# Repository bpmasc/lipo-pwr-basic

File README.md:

# lipo-pwr-basic
Simple LIPO battery power mgmt PCB.

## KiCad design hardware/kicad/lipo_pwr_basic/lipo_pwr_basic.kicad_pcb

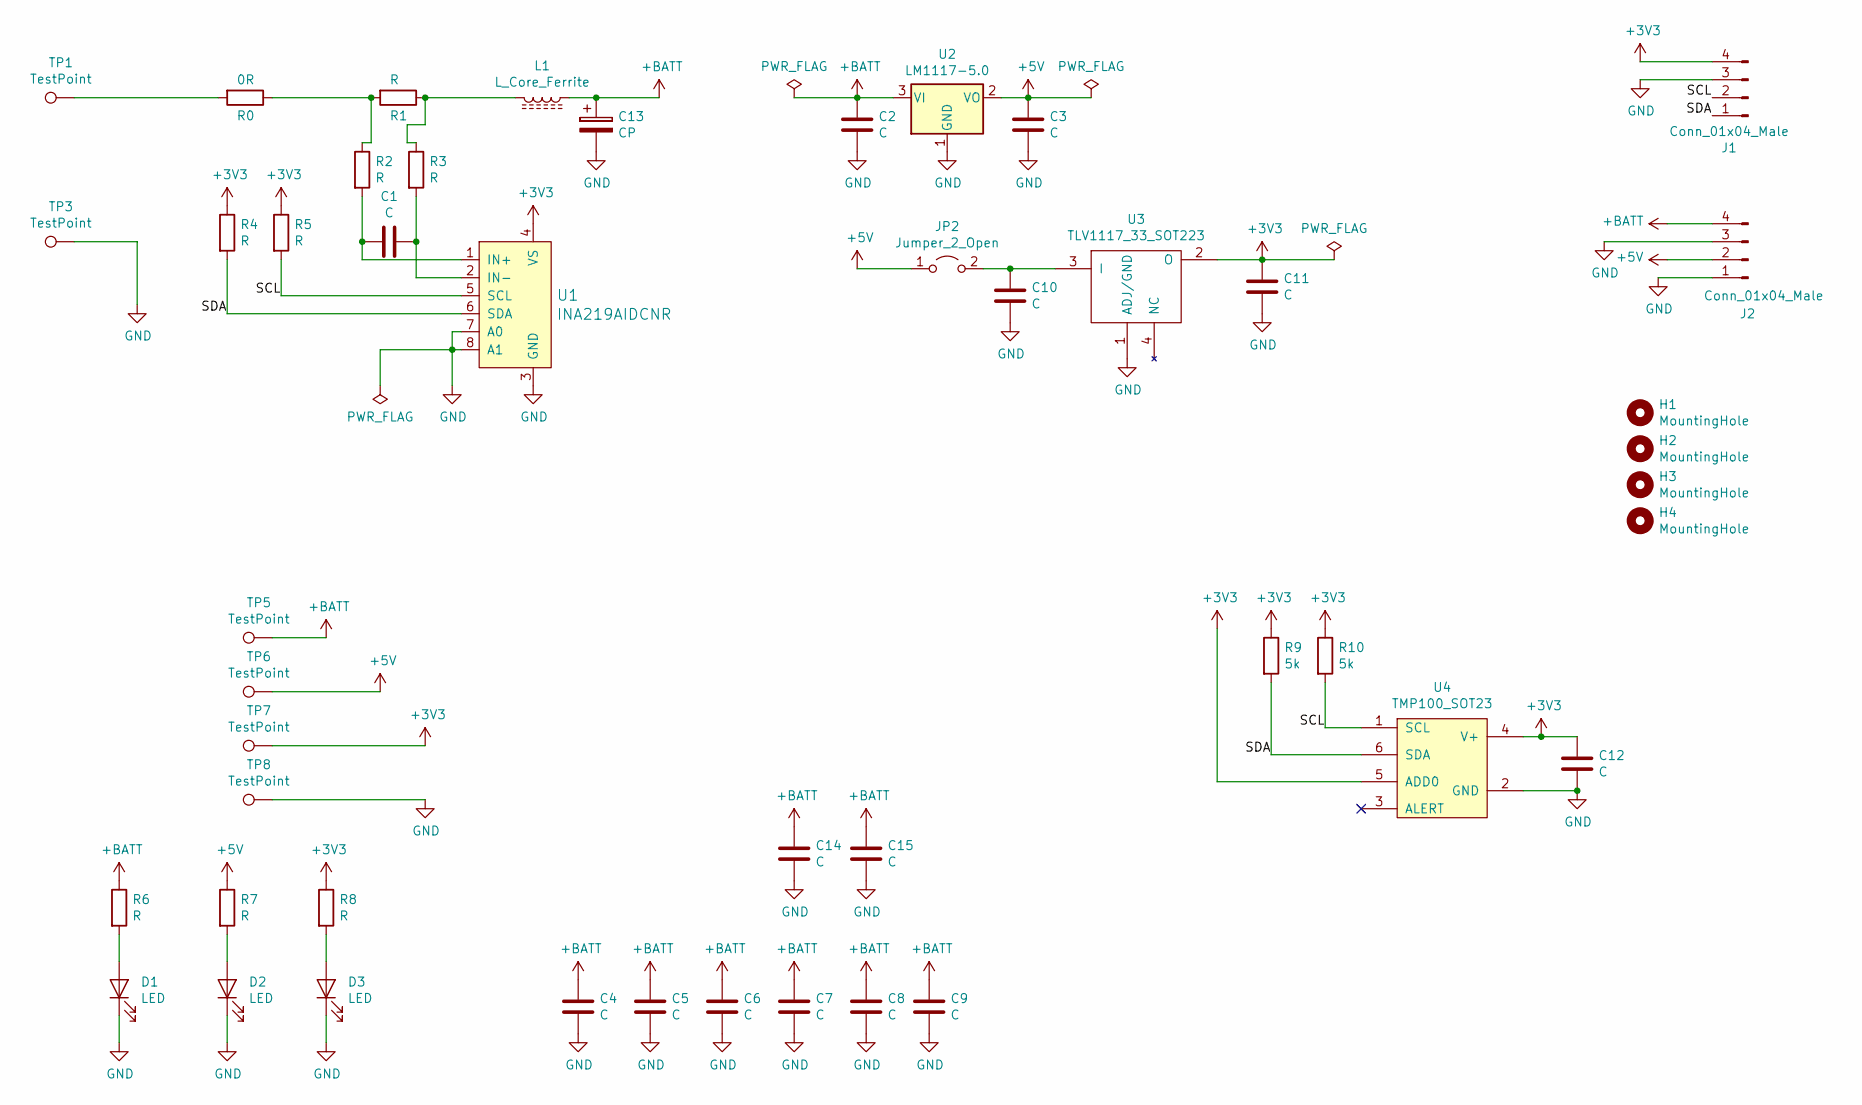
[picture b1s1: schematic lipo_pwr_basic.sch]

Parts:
C1, C2, C3, C10, C11, C12: C; C_0603
C4, C5, C6, C7, C8, C9, C14, C15: C; C_1206_HandSoldering
C13: CP; CP_Elec_6.3x5.7
D1, D2, D3: LED; LED_0603_1608Metric
H1, H2, H3, H4: MountingHole; MountingHole_2.2mm_M2
J1, J2: Conn_01x04_Male; Pin_Header_Straight_1x04_Pitch2.54mm
JP2: Jumper_2_Open; SolderJumper-2_P1.3mm_Open_Pad1.0x1.5mm
L1: L_Core_Ferrite; L_Wuerth_HCI-7030
R0: 0R; R_1206
R1: R; R_2512
R2, R3, R4, R5, R6, R7, R8: R; R_0603
R9, R10: 5k; R_0603
TP1, TP3: TestPoint; TestPoint_Pad_4.0x4.0mm
TP5, TP6, TP7, TP8: TestPoint; TestPoint_Pad_2.5x2.5mm
U1: INA219AIDCNR; SOT-23-8; MPN INA219AIDCNR; Digi-Key_PN 296-23770-1-ND
U2: LM1117-5.0; SOT-223
U3: TLV1117_33_SOT223; SOT-223
U4: TMP100_SOT23; SOT-23-6

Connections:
+3V3: C11.1, C12.1, J1.4, R4.1, R5.1, R8.1, R9.1, R10.1, TP7.1, U1.4 (VS), U3.2 (O), U4.4 (V+), U4.5 (ADD0)
+5V: C3.1, J2.2, JP2.1 (A), R7.1, TP6.1, U2.2 (VO)
+BATT: C2.1, C4.1, C5.1, C6.1, C7.1, C8.1, C9.1, C13.1, C14.1, C15.1, J2.4, L1.1, R6.1, TP5.1, U2.3 (VI)
/SCL: J1.2, R5.2, R10.2, U1.5 (SCL), U4.1 (SCL)
/SDA: J1.1, R4.2, R9.2, U1.6 (SDA), U4.6 (SDA)
GND: C2.2, C3.2, C4.2, C5.2, C6.2, C7.2, C8.2, C9.2, C10.2, C11.2, C12.2, C13.2, C14.2, C15.2, D1.1 (K), D2.1 (K), D3.1 (K), J1.3, J2.1, J2.3, TP3.1, TP8.1, U1.3 (GND), U1.7 (A0), U1.8 (A1), U2.1 (GND), U3.1 (ADJ/GND), U4.2 (GND)
unnamed: C1.1, R3.2, U1.2 (IN-)
unnamed: C1.2, R2.2, U1.1 (IN+)
unnamed: C10.1, JP2.2 (B), U3.3 (I)
unnamed: D1.2 (A), R6.2
unnamed: D2.2 (A), R7.2
unnamed: D3.2 (A), R8.2
unnamed: L1.2, R1.1, R3.1
unnamed: R0.1, R1.2, R2.1
unnamed: R0.2, TP1.1

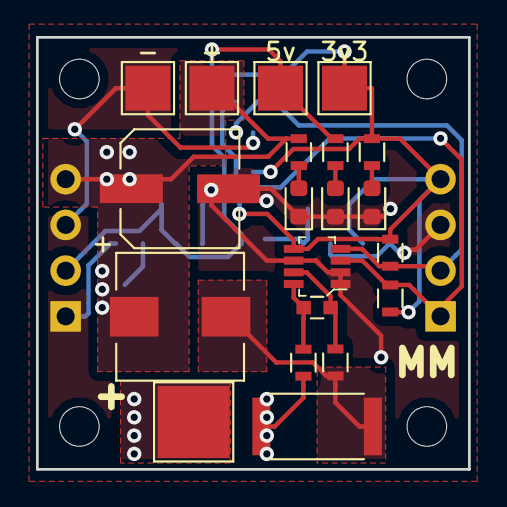
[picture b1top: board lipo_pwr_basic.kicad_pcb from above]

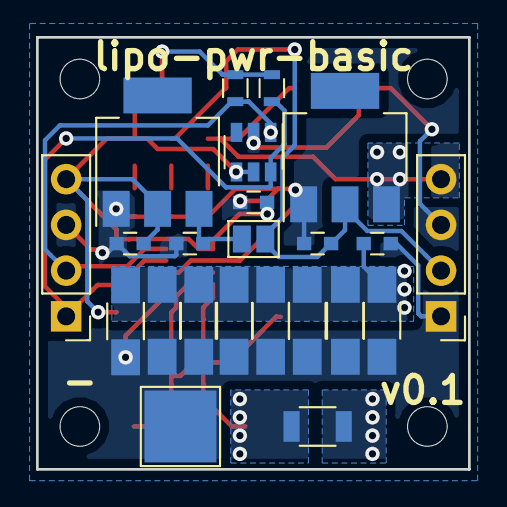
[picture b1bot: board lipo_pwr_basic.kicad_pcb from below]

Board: 2 copper layers, 24.0 x 24.0 mm, 47 parts (23 on the bottom side), 15 nets.

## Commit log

2019-04-28 Added Hardware version 0.1
2019-07-14 temp rev
